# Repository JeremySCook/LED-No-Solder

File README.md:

# LED-No-Solder
.8mm PCB that includes coin cell holder and LED that can be attached with no solder  
Available on Tindie: https://www.tindie.com/products/jeremycook/led-no-solder-3-pack/  
Build video: https://www.youtube.com/watch?v=3N0H6gIqDZk

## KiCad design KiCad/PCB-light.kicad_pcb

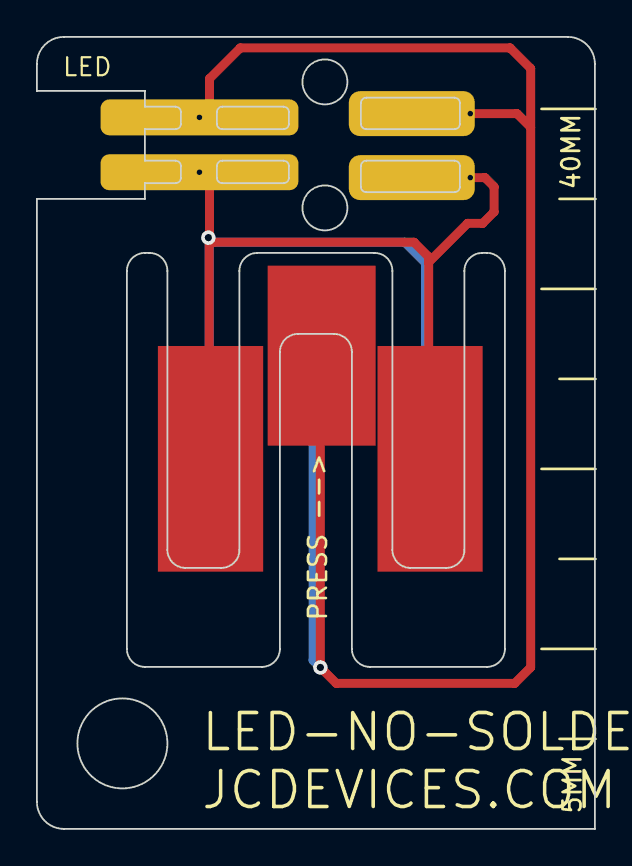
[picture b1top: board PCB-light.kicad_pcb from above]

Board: 2 copper layers, 31.0 x 44.0 mm, 4 parts (1 on the bottom side), 2 nets.

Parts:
CONTACTS-BATTERY1, CONTACTS-BATTERY2: pick-contact-jsc; pick-battery-jsc
D1, D1#2: LED; led-wrap-jsc

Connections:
unnamed: CONTACTS-BATTERY1.1 (POS1), CONTACTS-BATTERY1.3 (POS3), CONTACTS-BATTERY2.1 (POS1), CONTACTS-BATTERY2.3 (POS3), D1.2 (A), D1#2.2 (A)
unnamed: CONTACTS-BATTERY1.2 (GND), CONTACTS-BATTERY2.2 (GND), D1.1 (K), D1#2.1 (K)
